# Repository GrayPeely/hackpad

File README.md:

# Olo's Art Hackpad

This is my hackpad! I intend to use it for art programs, to use for switching controls and file configuartions (saving, closing, etc). The top right button will change what the controls are used for, while the rest are the controls. The OLED will show what control scheme it is on. 
## CAD Model
The model was designed within OnShape. I would've used SolidWorks as it is what I work with at school, but my home computer cannot run it well. However, I am happy with the design.

/>

## PCB 
The PCB was designed within KiCad. 

## Bill of Materials
 - 5x Cherry MX Switches
 - 5x Keycaps
 - 1x XIAO RP2040
 - 1x 0.91 inch OLED Display
 - 4x M3x16mm Screws
 - 4x M3 Nuts
 - 1x Case (2 Printed Parts)

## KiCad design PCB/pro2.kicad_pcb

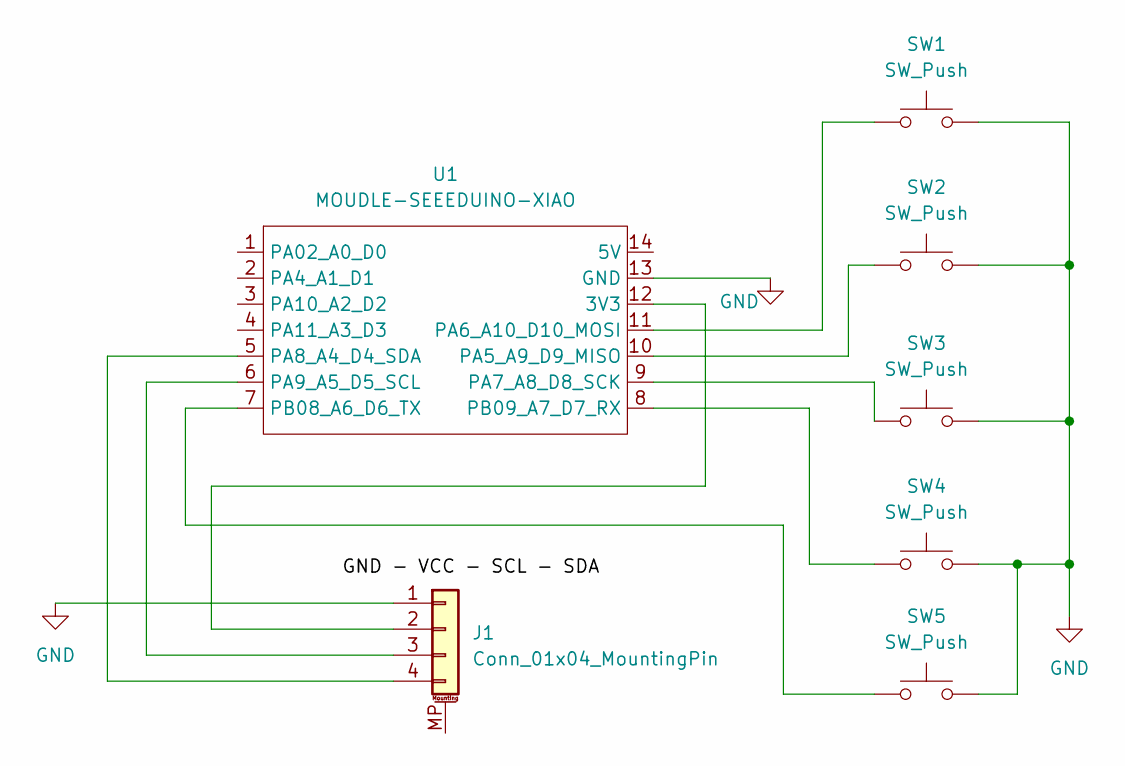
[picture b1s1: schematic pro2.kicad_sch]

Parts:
J1: Conn_01x04_MountingPin; SSD1306-0.91-OLED-4pin-128x32
SW1, SW2, SW3, SW4, SW5: SW_Push; SW_Cherry_MX_1.00u_PCB
U1: MOUDLE-SEEEDUINO-XIAO; XIAO-Generic-Hybrid-14P-2.54-21X17.8MM

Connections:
GND: J1.1, SW1.2, SW2.2, SW3.2, SW4.2, SW5.2, U1.13 (GND)
unnamed: J1.2, U1.12 (3V3)
unnamed: J1.3, U1.6 (PA9_A5_D5_SCL)
unnamed: J1.4, U1.5 (PA8_A4_D4_SDA)
unnamed: SW2.1, U1.10 (PA5_A9_D9_MISO)
unnamed: SW1.1, U1.11 (PA6_A10_D10_MOSI)
unnamed: SW3.1, U1.9 (PA7_A8_D8_SCK)
unnamed: SW5.1, U1.7 (PB08_A6_D6_TX)
unnamed: SW4.1, U1.8 (PB09_A7_D7_RX)

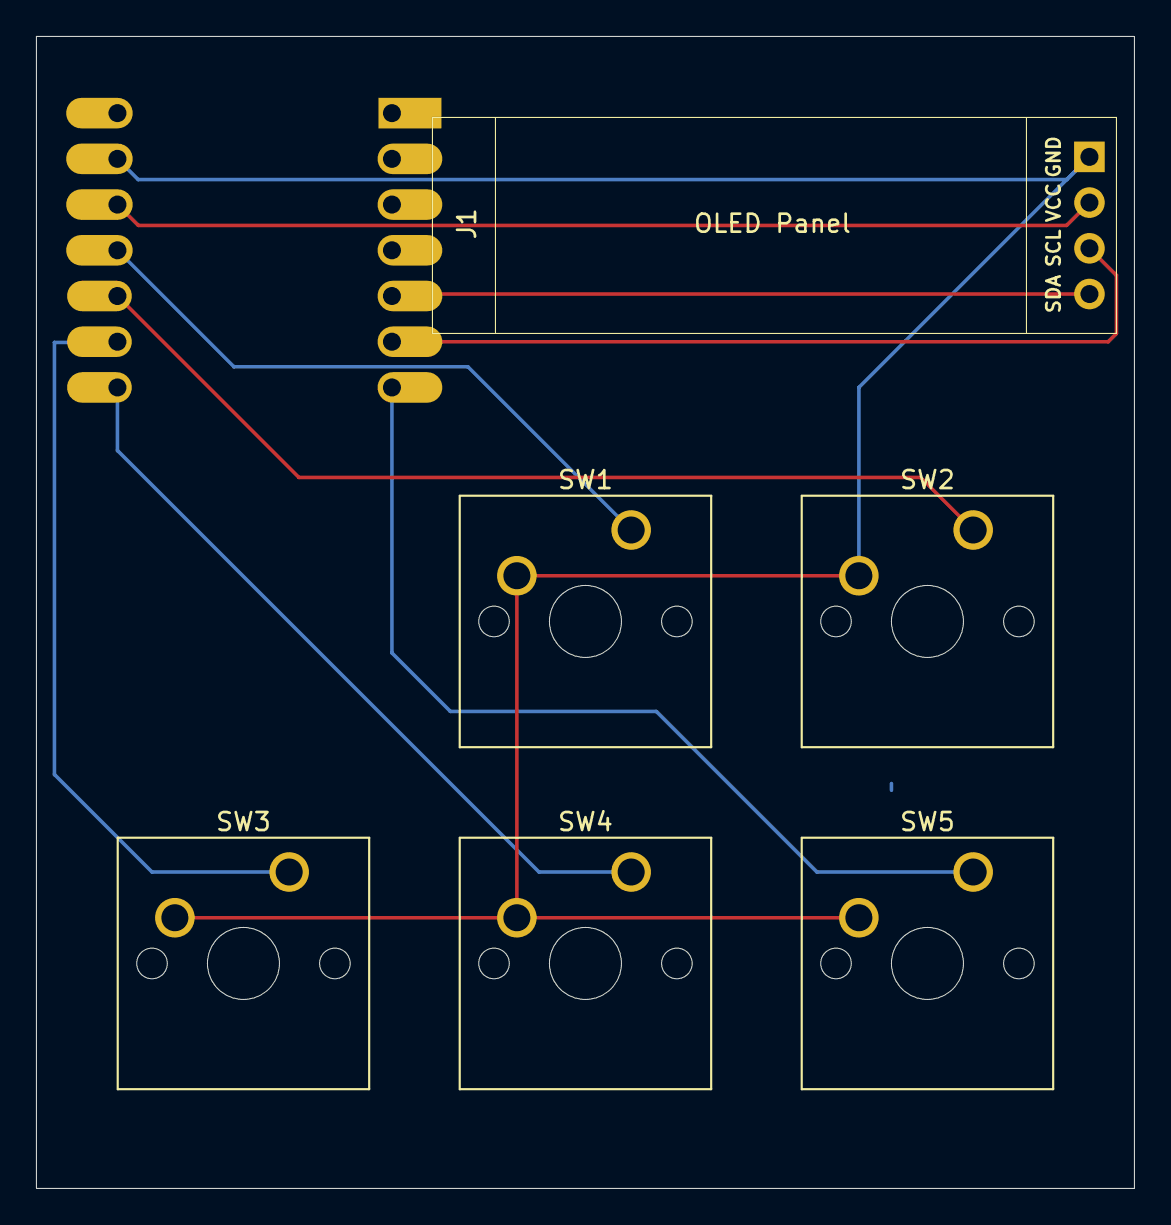
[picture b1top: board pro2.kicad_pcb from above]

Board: 2 copper layers, 61.0 x 64.0 mm, 7 parts (1 on the bottom side), 9 nets.

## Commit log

2026-02-15 test
2026-02-15 Create w
2026-02-16 Create test
2026-02-24 Create read
2026-02-24 Create a
2026-03-17 Create new
2026-03-17 Create dada
